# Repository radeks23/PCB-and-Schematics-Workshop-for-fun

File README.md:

# PCB-and-Schematics-for-fun
Projects with schematics and PCB designs.
## 7-28VDC to 3.3VDC
DC-DC step down converter with TPS54331

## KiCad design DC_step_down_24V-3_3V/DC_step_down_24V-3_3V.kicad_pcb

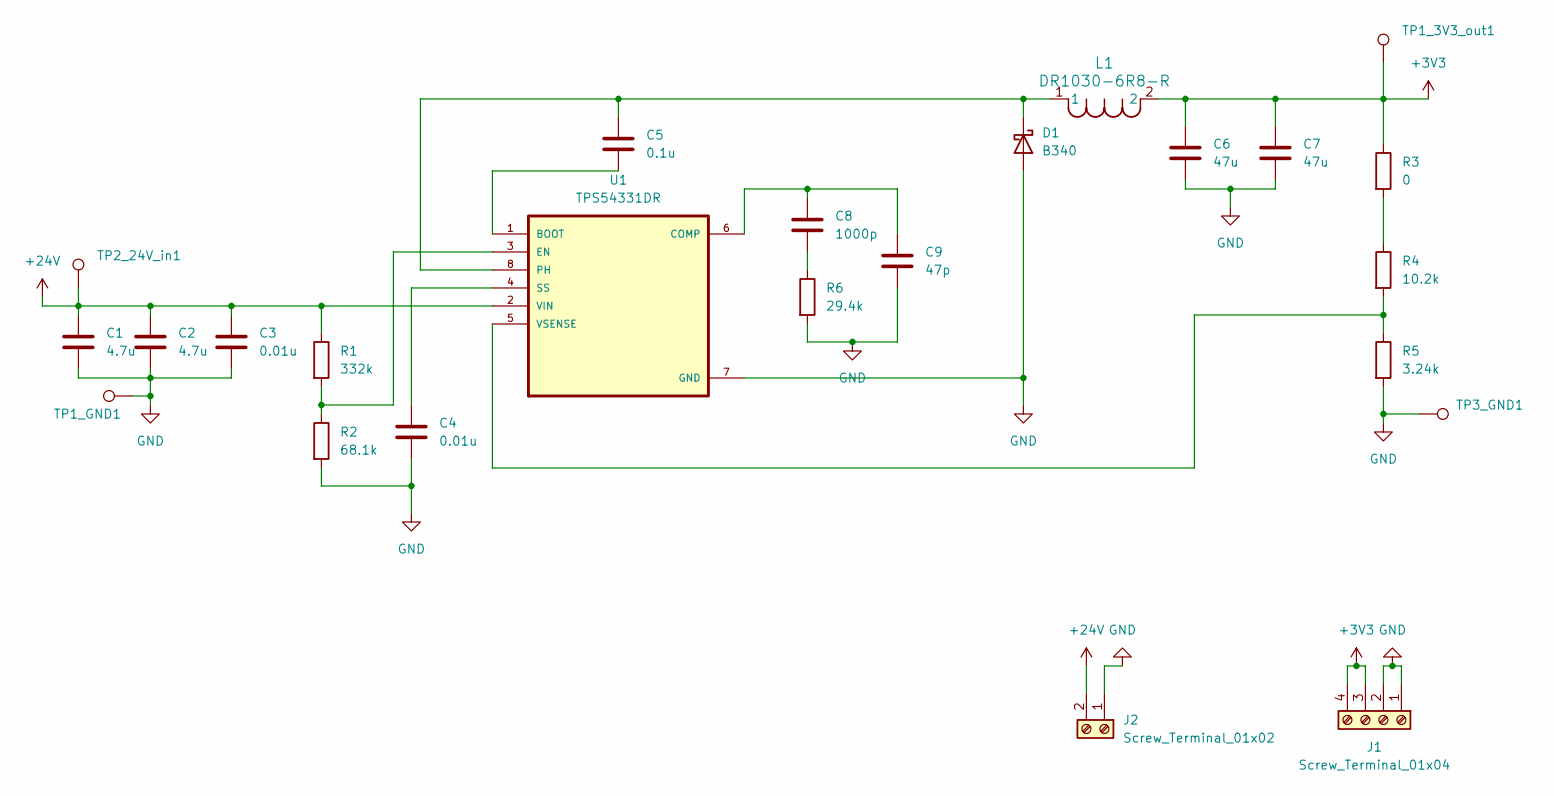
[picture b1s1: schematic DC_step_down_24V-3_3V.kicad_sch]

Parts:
C1, C2: 4.7u; C_0805_2012Metric_Pad1.18x1.45mm_HandSolder
C3, C4: 0.01u; C_0805_2012Metric_Pad1.18x1.45mm_HandSolder
C5: 0.1u; C_0805_2012Metric_Pad1.18x1.45mm_HandSolder
C6, C7: 47u; C_0805_2012Metric_Pad1.18x1.45mm_HandSolder
C8: 1000p; C_0805_2012Metric_Pad1.18x1.45mm_HandSolder
C9: 47p; C_0805_2012Metric_Pad1.18x1.45mm_HandSolder
D1: B340; D_SMC
J1: Screw_Terminal_01x04; TerminalBlock_Phoenix_MPT-0,5-4-2.54_1x04_P2.54mm_Horizontal
J2: Screw_Terminal_01x02; TerminalBlock_Phoenix_MPT-0,5-2-2.54_1x02_P2.54mm_Horizontal
L1: DR1030-6R8-R; DR1030
R1: 332k; R_0805_2012Metric_Pad1.20x1.40mm_HandSolder
R2: 68.1k; R_0805_2012Metric_Pad1.20x1.40mm_HandSolder
R3: 0; R_0805_2012Metric_Pad1.20x1.40mm_HandSolder
R4: 10.2k; R_0805_2012Metric_Pad1.20x1.40mm_HandSolder
R5: 3.24k; R_0805_2012Metric_Pad1.20x1.40mm_HandSolder
R6: 29.4k; R_0805_2012Metric_Pad1.20x1.40mm_HandSolder
TP1_3V3_out1, TP1_GND1, TP2_24V_in1, TP3_GND1: TestPoint_Loop_D2.50mm_Drill1.85mm
U1: TPS54331DR; SOIC127P599X175-8N

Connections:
+3V3: C6.1, C7.1, J1.3, J1.4, L1.2, R3.1, TP1_3V3_out1.1
+24V: C1.1, C2.1, C3.1, J2.2, R1.1, TP2_24V_in1.1, U1.2 (VIN)
GND: C1.2, C2.2, C3.2, C4.2, C6.2, C7.2, C9.2, D1.2 (A), J1.1, J1.2, J2.1, R2.2, R5.2, R6.2, TP1_GND1.1, TP3_GND1.1, U1.7 (GND)
unnamed: C8.2, R6.1
unnamed: C5.1, D1.1 (K), L1.1, U1.8 (PH)
unnamed: R3.2, R4.1
unnamed: C5.2, U1.1 (BOOT)
unnamed: C8.1, C9.1, U1.6 (COMP)
unnamed: R1.2, R2.1, U1.3 (EN)
unnamed: C4.1, U1.4 (SS)
unnamed: R4.2, R5.1, U1.5 (VSENSE)

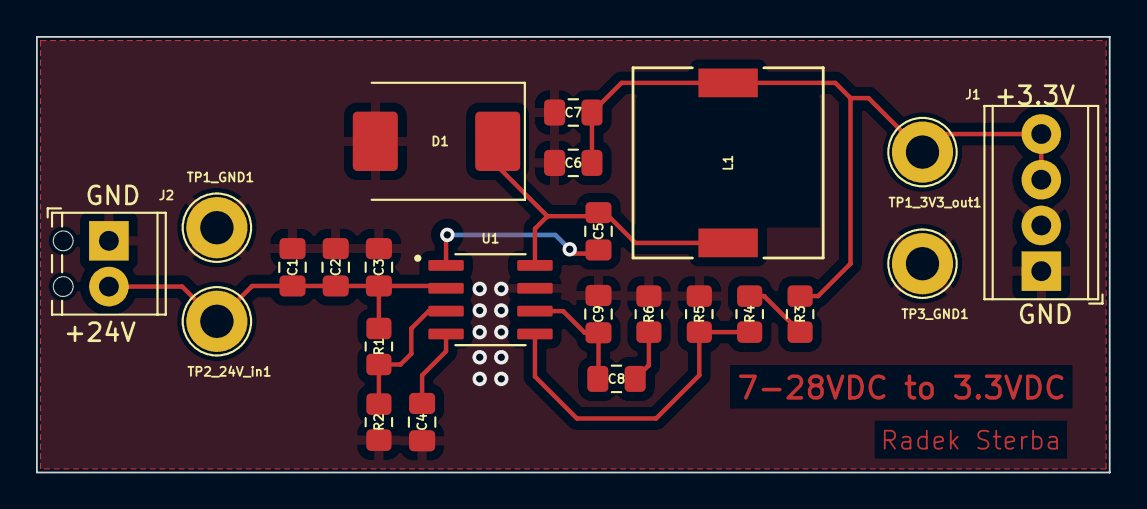
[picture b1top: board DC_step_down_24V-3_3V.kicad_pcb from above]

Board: 2 copper layers, 59.6 x 24.2 mm, 24 parts (0 on the bottom side), 11 nets.

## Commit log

2024-09-29 add files
    add all existed files (kicad files, gerber file)
2024-09-29 3D View
2024-09-29 remove temporarily
